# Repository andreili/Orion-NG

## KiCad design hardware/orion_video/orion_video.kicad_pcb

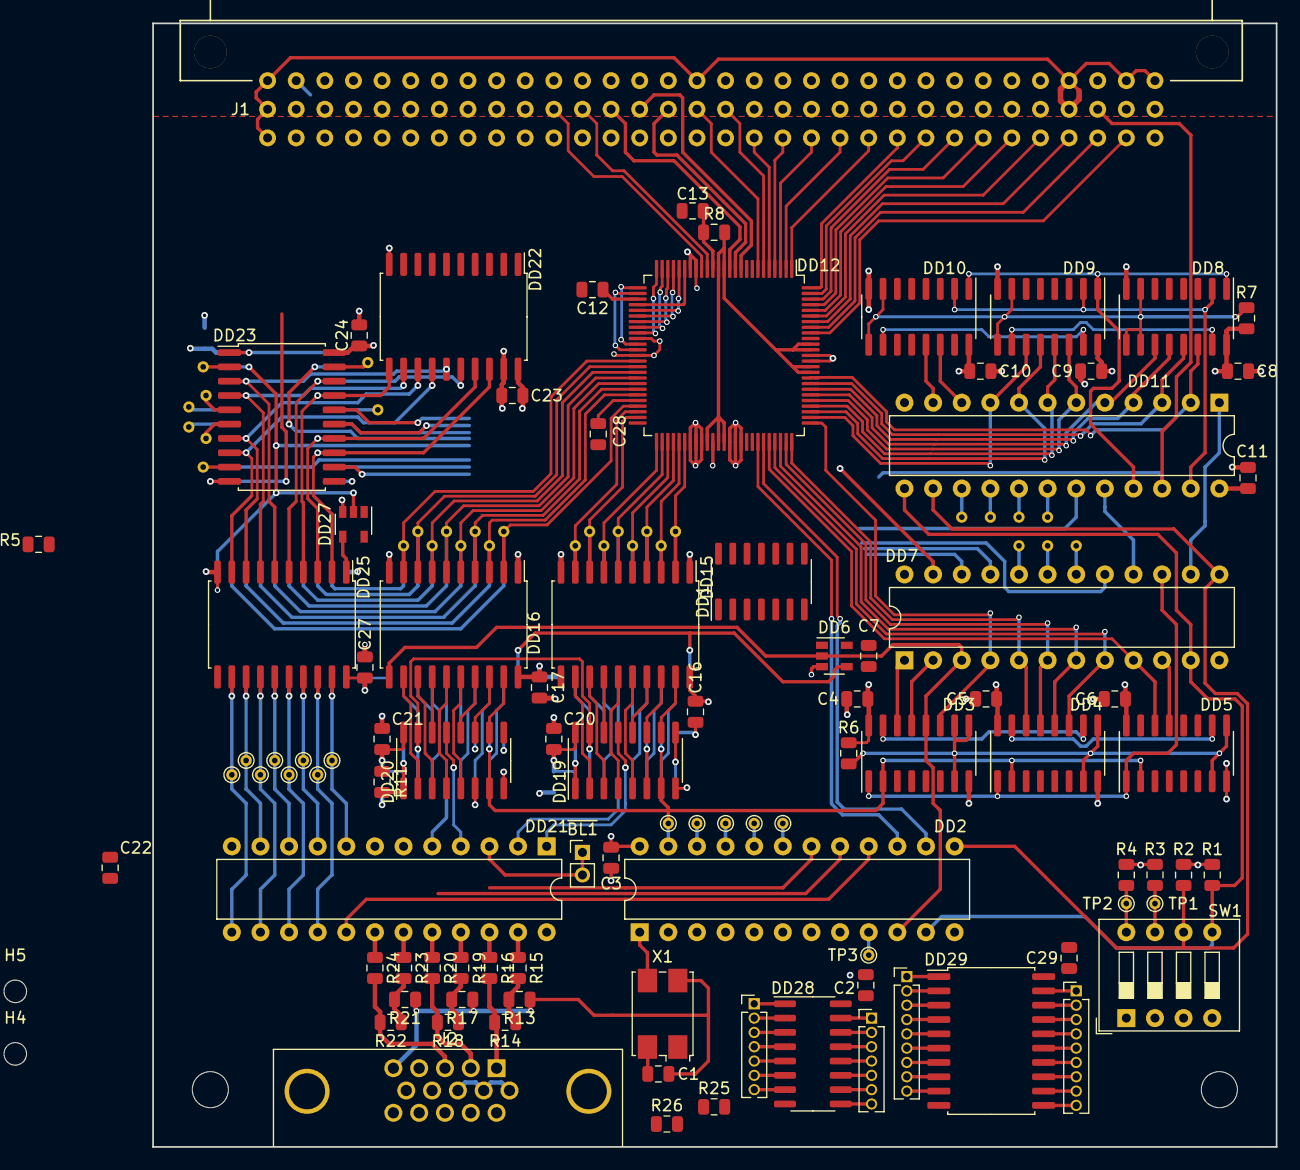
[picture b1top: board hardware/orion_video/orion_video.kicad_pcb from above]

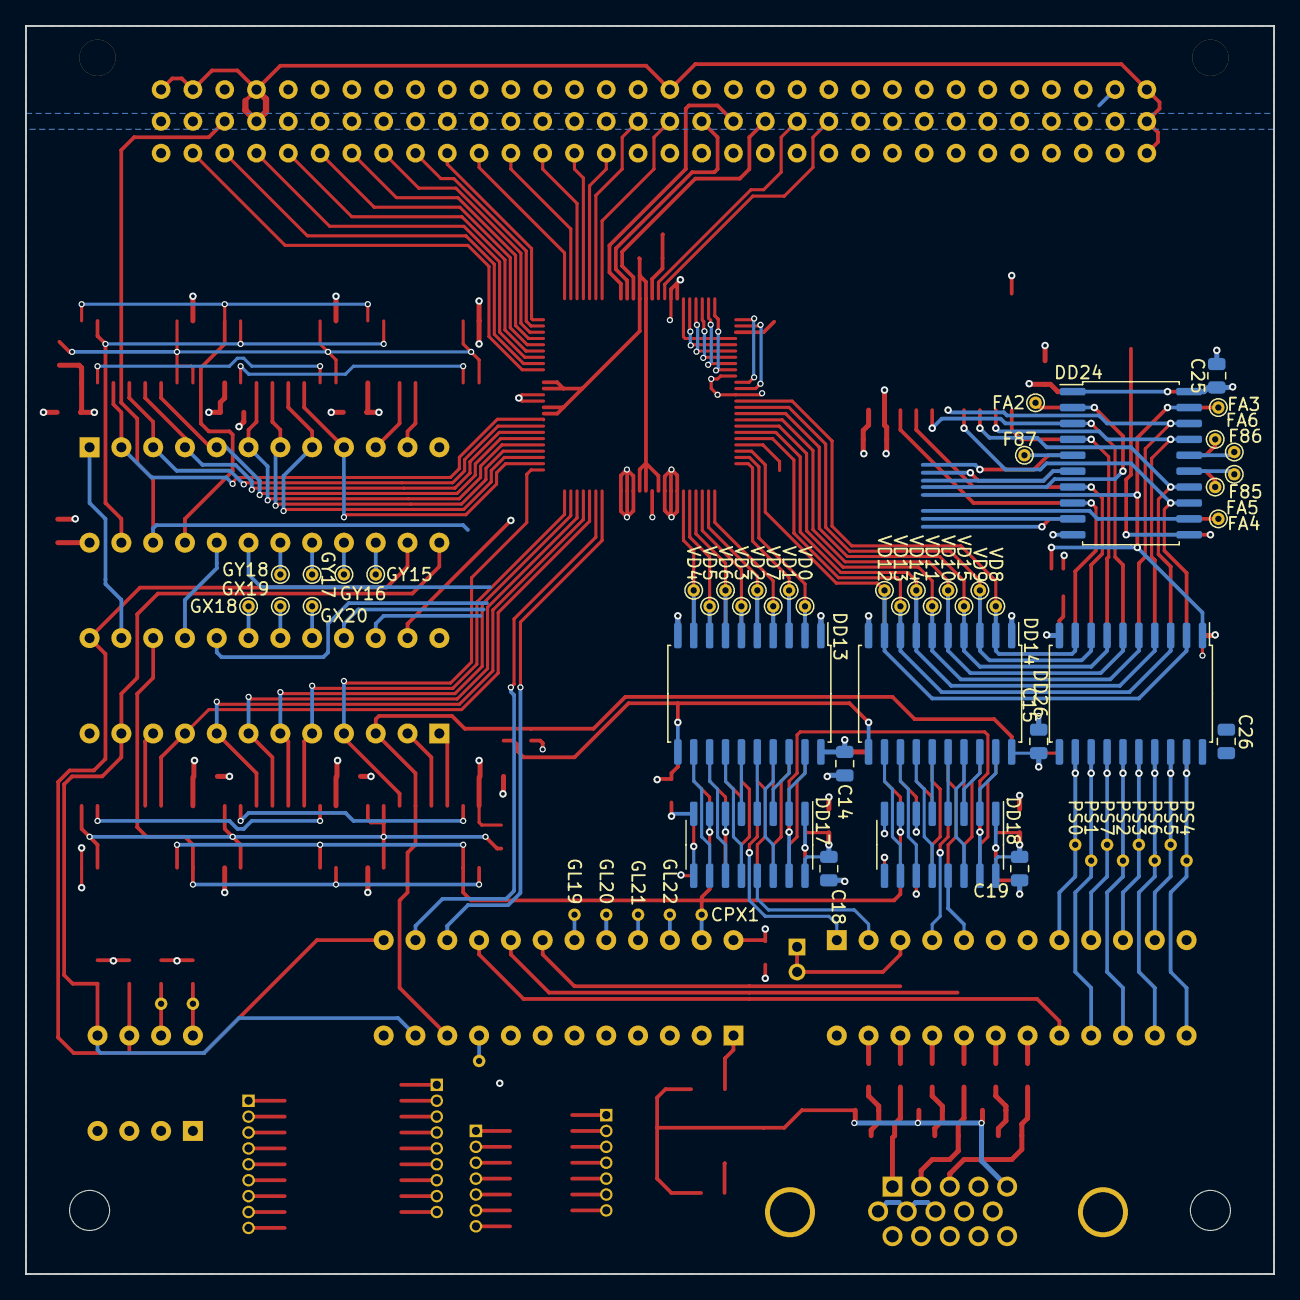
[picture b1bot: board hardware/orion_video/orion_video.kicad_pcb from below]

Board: 4 copper layers, 99.7 x 99.7 mm, 142 parts (43 on the bottom side), 232 nets.

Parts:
C1, C2, C3, C4, C5, C6, C7, C8, C9, C10, C11, C12, C13, C14, C15, C16, C17, C18, C19, C20, C21, C22, C23, C24, C25, C26, C27, C28, C29: 100n; C_0805_2012Metric
CPX1: TestPoint_Small; TestPoint_THTPad_D1.0mm_Drill0.5mm
DD1: TM2; SOIC-14_3.9x8.7mm_P1.27mm
DD2, DD7, DD11, DD21: ATF22V10; DIP-24_W7.62mm
DD3, DD4, DD5, DD8, DD9, DD10: IE18; SOIC-16_3.9x9.9mm_P1.27mm
DD6: 74AHCT1GU04; SOT-23-5
DD12: IDT7028PF; LQFP-100_14x14mm_P0.5mm
DD13, DD14, DD15, DD16: IR33; SOIC-20W_7.5x12.8mm_P1.27mm
DD17, DD18, DD19, DD20: IR10; SOIC-16_3.9x9.9mm_P1.27mm
DD22: AP6; SOIC-20W_7.5x12.8mm_P1.27mm
DD23, DD24: IR35; SOIC-20W_7.5x12.8mm_P1.27mm
DD25: 6; SOIC-20W_7.5x12.8mm_P1.27mm
DD26: IR23; SOIC-20W_7.5x12.8mm_P1.27mm
DD27: 74AHC1G04; SOT-23-5
DD28: Conn_02x08_Counter_Clockwise; SOIC-16_3.9x9.9mm_P1.27mm
DD29: Conn_02x10_Counter_Clockwise; SOIC-20W_7.5x12.8mm_P1.27mm
F85, F86, F87: FA2; TestPoint_THTPad_D1.0mm_Drill0.5mm
FA2: FA2; TestPoint_THTPad_D1.0mm_Drill0.5mm
FA3: FA3; TestPoint_THTPad_D1.0mm_Drill0.5mm
FA4: FA4; TestPoint_THTPad_D1.0mm_Drill0.5mm
FA5: FA5; TestPoint_THTPad_D1.0mm_Drill0.5mm
FA6: FA6; TestPoint_THTPad_D1.0mm_Drill0.5mm
GL19: GL14; TestPoint_THTPad_D1.0mm_Drill0.5mm
GL20: GL15; TestPoint_THTPad_D1.0mm_Drill0.5mm
GL21: GL16; TestPoint_THTPad_D1.0mm_Drill0.5mm
GL22: GL22; TestPoint_THTPad_D1.0mm_Drill0.5mm
GX18: GX18; TestPoint_THTPad_D1.0mm_Drill0.5mm
GX19: GX19; TestPoint_THTPad_D1.0mm_Drill0.5mm
GX20: GX20; TestPoint_THTPad_D1.0mm_Drill0.5mm
GY15: GY15; TestPoint_THTPad_D1.0mm_Drill0.5mm
GY16: GY16; TestPoint_THTPad_D1.0mm_Drill0.5mm
GY17: GY17; TestPoint_THTPad_D1.0mm_Drill0.5mm
GY18: GY22; TestPoint_THTPad_D1.0mm_Drill0.5mm
H1, H2: MountingHole; MountingHole_3.2mm_M3
H3, H4, H5, H6: MountingHole; MountingHole_2mm
J1: C96ABC; Socket_DIN41612-CaseC1-full-Male-96Pin-3rows
J2: VGA; DSUB-15-HD_Female_Horizontal_P2.29x1.98mm_EdgePinOffset3.03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
J3, J4: Conn_01x07_Female; PinHeader_1x07_P1.27mm_Vertical
J5, J6: Conn_01x09_Female; PinHeader_1x09_P1.27mm_Vertical
PS0, PS1, PS2, PS3, PS4, PS5, PS6, PS7: TestPoint_Small; TestPoint_THTPad_D1.0mm_Drill0.5mm
R1, R2, R3, R4, R5, R6, R7, R15, R19, R23: 1K; R_0805_2012Metric
R8, R11: 1k; R_0805_2012Metric
R13, R14, R17, R18, R21, R22: 470; R_0805_2012Metric
R16, R20, R24: 510; R_0805_2012Metric
R25, R26: 47; R_0805_2012Metric
SW1: SW_DIP_04; SW_DIP_SPSTx04_Slide_9.78x12.34mm_W7.62mm_P2.54mm
TP1: SW2; TestPoint_THTPad_D1.0mm_Drill0.5mm
TP2: SW3; TestPoint_THTPad_D1.0mm_Drill0.5mm
TP3: GL13; TestPoint_THTPad_D1.0mm_Drill0.5mm
VD0, VD1, VD2, VD3, VD4, VD5, VD6, VD7, VD8, VD9, VD10, VD11, VD12, VD13, VD14, VD15: TestPoint_Small; TestPoint_THTPad_D1.0mm_Drill0.5mm
X1: 50MHz; Crystal_SMD_7050-4Pin_7.0x5.0mm

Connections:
/CL0: DD6.4, DD13.11 (LE), DD14.11 (LE)
/CL1: DD2.10 (I10), DD3.12 (4), DD6.2, DD7.3 (I3), DD15.11 (LE), DD16.11 (LE)
/CPX: CPX1.1, DD2.23 (IO1), DD3.2 (C), DD4.2 (C), DD5.2 (C), DD17.7 (C), DD18.7 (C), DD19.7 (C), DD20.7 (C)
/FEND: DD1.3 (C), DD1.11 (C), DD11.22 (IO2), J1.30b (30B)
/HS: DD7.21 (IO3), R25.2
/SR16: DD7.23 (IO1), DD23.16 (6)
/VB0: DD1.12 (D), DD23.12 (4)
/VB1: DD1.2 (D), DD23.15 (5)
/VD0: DD12.48 (Q8), DD13.2 (0), DD15.9 (7), VD0.1
/VD1: DD12.49 (Q9), DD13.3 (1), DD15.8 (6), VD1.1
/VD2: DD12.52 (Q11), DD13.5 (3), DD15.6 (4), VD2.1
/VD3: DD12.53 (Q12), DD13.6 (4), DD15.5 (3), VD3.1
/VD4: DD12.56 (Q15), DD13.9 (7), DD15.2 (0), VD4.1
/VD5: DD12.55 (Q14), DD13.8 (6), DD15.3 (1), VD5.1
/VD6: DD12.54 (Q13), DD13.7 (5), DD15.4 (2), VD6.1
/VD7: DD12.51 (Q10), DD13.4 (2), DD15.7 (5), VD7.1
/VD8: DD12.39 (Q0), DD14.2 (0), DD16.9 (7), DD26.9 (7), VD8.1
/VD9: DD12.40 (Q1), DD14.3 (1), DD16.8 (6), DD26.8 (6), VD9.1
/VD10: DD12.42 (Q3), DD14.5 (3), DD16.6 (4), DD26.6 (4), VD10.1
/VD11: DD12.43 (Q4), DD14.6 (4), DD16.5 (3), DD26.5 (3), VD11.1
/VD12: DD12.47 (Q7), DD14.9 (7), DD16.2 (0), DD26.2 (0), VD12.1
/VD13: DD12.45 (Q6), DD14.8 (6), DD16.3 (1), DD26.3 (1), VD13.1
/VD14: DD12.44 (Q5), DD14.7 (5), DD16.4 (2), DD26.4 (2), VD14.1
/VD15: DD12.41 (Q2), DD14.4 (2), DD16.7 (5), DD26.7 (5), VD15.1
/VM0: DD2.6 (I6), DD24.9 (3)
/VM1: DD2.7 (I7), DD24.6 (2)
/VM2: DD2.5 (I5), DD18.9 (R), DD24.2 (0)
/VM3: DD2.4 (I4), DD24.19 (7), DD26.1 (OE), DD27.2
/VM4: DD2.8 (I8), DD24.12 (4)
/VS: DD11.19 (IO5), R26.2
/VS0: DD2.18 (IO6), DD21.7 (I7)
/VS1: DD2.17 (IO7), DD21.6 (I6)
/VS2: DD2.16 (IO8), DD21.17 (IO7)
/video_gen/SR0: DD2.11 (I11), DD7.11 (I11), DD11.13 (I12), R1.2, SW1.5
/video_gen/SR1: DD2.13 (I12), DD7.13 (I12), DD11.14 (IO10), R2.2, SW1.6
/video_gen/X0: DD3.14 (1), DD7.1 (I1/CLK)
/video_gen/X1: DD3.13 (2), DD7.2 (I2)
/video_gen/X3: DD3.11 (8), DD7.4 (I4), DD12.76 (A8)
/video_gen/X4: DD4.14 (1), DD7.5 (I5), DD12.75 (A9)
/video_gen/X5: DD4.13 (2), DD7.6 (I6), DD12.74 (A10)
/video_gen/X6: DD4.12 (4), DD7.7 (I7), DD12.73 (A11)
/video_gen/X7: DD4.11 (8), DD7.8 (I8), DD12.72 (A12)
/video_gen/X8: DD5.14 (1), DD7.9 (I9), DD12.71 (A13)
/video_gen/X9: DD5.13 (2), DD7.10 (I10)
/video_gen/XH0: DD3.15 (P2), DD4.10 (P1)
/video_gen/XH1: DD4.15 (P2), DD5.10 (P1)
/video_gen/XLE: DD7.14 (IO10), DD11.1 (I1/CLK)
/video_gen/Y0: DD8.14 (1), DD11.2 (I2), DD12.84 (A0)
/video_gen/Y1: DD8.13 (2), DD11.3 (I3), DD12.83 (A1)
/video_gen/Y2: DD8.12 (4), DD11.4 (I4), DD12.82 (A2)
/video_gen/Y3: DD8.11 (8), DD11.5 (I5), DD12.81 (A3)
/video_gen/Y4: DD9.14 (1), DD11.6 (I6), DD12.80 (A4)
/video_gen/Y5: DD9.13 (2), DD11.7 (I7), DD12.79 (A5)
/video_gen/Y6: DD9.12 (4), DD11.8 (I8), DD12.78 (A6)
/video_gen/Y7: DD9.11 (8), DD11.9 (I9), DD12.77 (A7)
/video_gen/Y8: DD10.14 (1), DD11.10 (I10)
/video_gen/Y9: DD10.13 (2), DD11.11 (I11)
/video_gen/YH0: DD8.15 (P2), DD9.10 (P1)
/video_gen/YH1: DD9.15 (P2), DD10.10 (P1)
/video_gen/~BV: DD7.16 (IO8), DD11.20 (IO4)
/video_gen/~XRES: DD3.1 (RC), DD4.1 (RC), DD5.1 (RC), DD7.15 (IO9)
/video_gen/~YRES: DD8.1 (RC), DD9.1 (RC), DD10.1 (RC), DD11.21 (IO3)
/video_regs/A0: DD12.92 (A0), J1.31a (31A)
/video_regs/A1: DD12.93 (A1), J1.30a (30A)
/video_regs/A2: DD12.94 (A2), J1.29a (29A)
/video_regs/A3: DD12.95 (A3), J1.28a (28A)
/video_regs/A4: DD12.96 (A4), J1.27a (27A)
/video_regs/A5: DD12.97 (A5), J1.26a (26A)
/video_regs/A6: DD12.98 (A6), J1.25a (25A)
/video_regs/A7: DD12.99 (A7), J1.24a (24A)
/video_regs/A8: DD12.100 (A8), J1.23a (23A)
/video_regs/A9: DD12.1 (A9), J1.22a (22A)
/video_regs/A10: DD12.2 (A10), J1.21a (21A)
/video_regs/A11: DD12.3 (A11), J1.20a (20A)
/video_regs/A12: DD12.4 (A12), J1.19a (19A)
/video_regs/A13: DD12.5 (A13), J1.18a (18A)
/video_regs/BD0: DD12.27 (Q8), DD12.37 (Q0), DD22.18 (B0), DD23.13 (4), DD24.8 (3), DD25.2 (0)
/video_regs/BD1: DD12.26 (Q9), DD12.36 (Q1), DD22.17 (B1), DD23.14 (5), DD24.7 (2), DD25.3 (1)
/video_regs/BD2: DD12.24 (Q11), DD12.33 (Q3), DD22.16 (B2), DD23.18 (7), DD24.3 (0), DD25.5 (3)
/video_regs/BD3: DD12.23 (Q12), DD12.32 (Q4), DD22.15 (B3), DD23.3 (0), DD24.18 (7), DD25.6 (4)
/video_regs/BD4: DD12.20 (Q15), DD12.29 (Q7), DD22.14 (B4), DD23.8 (3), DD24.13 (4), DD25.9 (7)
/video_regs/BD5: DD12.21 (Q14), DD12.30 (Q6), DD22.13 (B5), DD23.7 (2), DD24.14 (5), DD25.8 (6)
/video_regs/BD6: DD12.22 (Q13), DD12.31 (Q5), DD22.12 (B6), DD23.4 (1), DD24.17 (6), DD25.7 (5)
/video_regs/BD7: DD12.25 (Q10), DD12.34 (Q2), DD22.11 (B7), DD23.17 (6), DD24.4 (1), DD25.4 (2)
/video_regs/D0: DD22.2 (A0), J1.9a (9A)
/video_regs/D1: DD22.3 (A1), J1.8a (8A)
/video_regs/D2: DD22.4 (A2), J1.7a (7A)
/video_regs/D3: DD22.5 (A3), J1.6a (6A)
/video_regs/D4: DD22.6 (A4), J1.5a (5A)
/video_regs/D5: DD22.7 (A5), J1.4a (4A)
/video_regs/D6: DD22.8 (A6), J1.3a (3A)
/video_regs/D7: DD22.9 (A7), J1.2a (2A)
/video_regs/MA14: DD12.6 (A14), J1.17b (17B)
/video_regs/MA15: DD12.7 (A15), J1.16b (16B)
/video_regs/MA16: DD12.11 (UB), J1.15b (15B)
/video_regs/P0: DD17.13 (QH), DD21.2 (I2)
/video_regs/P1: DD18.13 (QH), DD21.5 (I5)
/video_regs/P2: DD19.13 (QH), DD21.1 (I1/CLK)
/video_regs/P3: DD20.13 (QH), DD21.4 (I4)
/video_regs/PF8: DD24.11 (C), J1.7b (7B)
/video_regs/PFA: DD23.11 (C), J1.8b (8B)
/video_regs/PFC: DD25.11 (C), J1.6b (6B)
/video_regs/PS0: DD21.8 (I8), DD25.19 (0), DD26.12 (7), PS0.1
/video_regs/PS1: DD21.16 (IO8), DD25.18 (1), DD26.13 (6), PS1.1
/video_regs/PS2: DD21.15 (IO9), DD25.16 (3), DD26.15 (4), PS2.1
/video_regs/PS3: DD21.10 (I10), DD25.15 (4), DD26.16 (3), PS3.1
/video_regs/PS4: DD21.13 (I12), DD25.12 (7), DD26.19 (0), PS4.1
/video_regs/PS5: DD21.11 (I11), DD25.13 (6), DD26.18 (1), PS5.1
/video_regs/PS6: DD21.14 (IO10), DD25.14 (5), DD26.17 (2), PS6.1
/video_regs/PS7: DD21.9 (I9), DD25.17 (2), DD26.14 (5), PS7.1
/video_regs/~MRD: DD12.17 (~OE), J1.11b (11B)
/video_regs/~MWR: DD12.16 (R/~W), J1.12b (12B)
/video_regs/~RD: DD22.1 (A/B), J1.14c (14C)
/video_regs/~RES: DD23.1 (R), DD24.1 (R), J1.2c (2C)
/video_regs/~UB: DD12.10 (LB), J1.14b (14B)
/video_regs/~VCE: DD12.12 (~CE0), J1.13b (13B)
/~BE: DD7.22 (IO2), DD17.15 (L), DD18.15 (L), DD19.15 (L), DD20.15 (L), DD26.11 (C)
/~BL: DD7.17 (IO7), DD21.3 (I3)
GND: C1.2, C2.2, C3.2, C4.2, C5.2, C6.2, C7.2, C8.2, C9.2, C10.2, C11.2, C12.2, C13.2, C14.2, C15.2, C16.2, C17.2, C18.2, C19.2, C20.2, C21.2, C22.2, C23.2, C24.2, C25.2, C26.2, C27.2, C28.2, C29.2, DD1.7 (GND), DD2.12 (GND), DD3.8 (GND), DD4.8 (GND), DD5.8 (GND), DD6.3 (GND), DD7.12 (GND), DD8.8 (GND), DD9.8 (GND), DD10.8 (GND), DD11.12 (GND), DD12.18 (GND), DD12.19 (GND), DD12.35 (GND), DD12.38 (GND), DD12.57 (GND), DD12.58 (GND), DD12.59 (~OE), DD12.61 (GND), DD12.64 (~CE0), DD12.65 (UB), DD12.66 (LB), DD12.87 (M/~S), DD12.88 (GND), DD13.1 (OE), DD13.10 (GND), DD14.1 (OE), DD14.10 (GND), DD15.1 (OE), DD15.10 (GND), DD16.1 (OE), DD16.10 (GND), DD17.6 (CI), DD17.8 (GND), DD18.6 (CI), DD18.8 (GND), DD19.6 (CI), DD19.8 (GND), DD20.6 (CI), DD20.8 (GND), DD21.12 (GND), DD22.10 (GND), DD22.19 (OE), DD23.10 (GND), DD24.10 (GND), DD25.10 (GND), DD26.10 (GND), DD27.3 (GND), DD28.8, DD29.10, J1.1a (1A), J1.1b (1B), J1.1c (1C), J1.16c (16C), J1.29b (29B), J1.29c (29C), J1.31c (31C), J1.32c (32C), J2.5, J2.6, J2.7, J2.8, J2.10, R13.1, R17.1, R21.1, SW1.1, SW1.2, SW1.3, SW1.4, X1.2 (GND)
MVP: DD12.13 (CE1), DD12.14 (~SEM), DD12.60 (R/~W), DD12.62 (~SEM), DD12.63 (CE1), DD12.85 (~INTL), DD12.86 (~BUSY), DD12.89 (~BUSY), DD12.90 (~INTL), R8.2
unnamed: DD1.1 (R), DD1.4 (S), DD1.10 (S), DD1.13 (R), R5.2
unnamed: DD1.6 (Q), DD2.3 (I3)
unnamed: DD1.8 (Q), DD2.2 (I2)
unnamed: DD2.1 (I1/CLK), X1.3 (OUT)
unnamed: DD2.9 (I9), TP3.1
unnamed: DD2.19 (IO5), GL19.1
unnamed: DD2.20 (IO4), GL20.1
unnamed: DD2.21 (IO3), GL21.1
unnamed: DD2.22 (IO2), GL22.1
unnamed: DD3.7 (V1), DD3.9 (W), DD3.10 (P1), DD4.7 (V1), DD4.9 (W), DD5.7 (V1), DD5.9 (W), R6.2
unnamed: DD7.18 (IO6), GX18.1
unnamed: DD7.19 (IO5), GX19.1
unnamed: DD7.20 (IO4), GX20.1
unnamed: DD8.2 (C), DD9.2 (C), DD10.2 (C), DD11.23 (IO1)
unnamed: DD8.7 (V1), DD8.9 (W), DD8.10 (P1), DD9.7 (V1), DD9.9 (W), DD10.7 (V1), DD10.9 (W), R7.2
unnamed: DD11.15 (IO9), GY15.1
unnamed: DD11.16 (IO8), GY16.1
unnamed: DD11.17 (IO7), GY17.1
unnamed: DD11.18 (IO6), GY18.1
unnamed: DD2.15 (IO9), DD12.69 (A15)
unnamed: DD2.14 (IO10), DD12.70 (A14)
unnamed: DD17.1 (SI), DD17.9 (R), DD18.1 (SI), DD19.1 (SI), DD19.9 (R), DD20.1 (SI), DD20.9 (R), R11.2
unnamed: DD21.18 (IO6), R24.1
unnamed: DD21.19 (IO5), R23.1
unnamed: DD21.20 (IO4), R20.1
unnamed: DD21.21 (IO3), R19.1
unnamed: DD21.22 (IO2), R16.1
unnamed: DD21.23 (IO1), R15.1
unnamed: DD23.2 (0), FA3.1
unnamed: DD23.5 (1), FA6.1
unnamed: DD23.6 (2), FA5.1
unnamed: DD23.9 (3), FA4.1
unnamed: DD23.19 (7), FA2.1
unnamed: DD24.5 (1), F87.1
unnamed: DD24.15 (5), F85.1
unnamed: DD24.16 (6), F86.1
unnamed: DD25.1 (OE), DD27.4
unnamed: DD28.1, J3.1
unnamed: DD28.2, J3.2
unnamed: DD28.3, J3.3
unnamed: DD28.4, J3.4
unnamed: DD28.5, J3.5
unnamed: DD28.6, J3.6
unnamed: DD28.7, J3.7
unnamed: DD28.9, J4.7
unnamed: DD28.10, J4.6
unnamed: DD28.11, J4.5
unnamed: DD28.12, J4.4
unnamed: DD28.13, J4.3
unnamed: DD28.14, J4.2
unnamed: DD28.15, J4.1
unnamed: DD29.1, J5.1
unnamed: DD29.2, J5.2
unnamed: DD29.3, J5.3
unnamed: DD29.4, J5.4
unnamed: DD29.5, J5.5
unnamed: DD29.6, J5.6
unnamed: DD29.7, J5.7
unnamed: DD29.8, J5.8
unnamed: DD29.9, J5.9
unnamed: DD29.11, J6.9
unnamed: DD29.12, J6.8
unnamed: DD29.13, J6.7
unnamed: DD29.14, J6.6
unnamed: DD29.15, J6.5
unnamed: DD29.16, J6.4
unnamed: DD29.17, J6.3
unnamed: DD29.18, J6.2
unnamed: DD29.19, J6.1
unnamed: J2.1, R14.2, R16.2
unnamed: J2.2, R18.2, R20.2
unnamed: J2.3, R22.2, R24.2
unnamed: J2.13, R25.1
unnamed: J2.14, R26.1
unnamed: R3.2, SW1.7, TP1.1
unnamed: R4.2, SW1.8, TP2.1
unnamed: R13.2, R14.1, R15.2
unnamed: R17.2, R18.1, R19.2
unnamed: R21.2, R22.1, R23.2
VCC: C1.1, C2.1, C3.1, C4.1, C5.1, C6.1, C7.1, C8.1, C9.1, C10.1, C11.1, C12.1, C13.1, C14.1, C15.1, C16.1, C17.1, C18.1, C19.1, C20.1, C21.1, C22.1, C23.1, C24.1, C25.1, C26.1, C27.1, C28.1, C29.1, DD1.14 (VCC), DD2.24 (VCC), DD3.16 (VCC), DD4.16 (VCC), DD5.16 (VCC), DD6.5 (VCC), DD7.24 (VCC), DD8.16 (VCC), DD9.16 (VCC), DD10.16 (VCC), DD11.24 (VCC), DD12.15 (VCC), DD12.28 (VCC), DD12.46 (VCC), DD13.20 (VCC), DD14.20 (VCC), DD15.20 (VCC), DD16.20 (VCC), DD17.16 (VCC), DD18.16 (VCC), DD19.16 (VCC), DD20.16 (VCC), DD21.24 (VCC), DD22.20 (VCC), DD23.20 (VCC), DD24.20 (VCC), DD25.20 (VCC), DD26.20 (VCC), DD27.5 (VCC), DD28.16, DD29.20, J1.3b (3B), J1.3c (3C), J1.18b (18B), J1.18c (18C), J1.20b (20B), J1.20c (20C), R1.1, R2.1, R3.1, R4.1, R5.1, R6.1, R7.1, R8.1, R11.1, X1.4 (V+)
VL0: DD13.19 (0), DD17.2 (0)
VL1: DD13.18 (1), DD17.3 (1)
VL2: DD13.16 (3), DD17.4 (2)
VL3: DD13.15 (4), DD17.5 (3)
VL4: DD13.12 (7), DD17.10 (4)
VL5: DD13.13 (6), DD17.11 (5)
VL6: DD13.14 (5), DD17.12 (6)
VL7: DD13.17 (2), DD17.14 (7)
VL8: DD14.19 (0), DD18.2 (0)
VL9: DD14.18 (1), DD18.3 (1)
VL10: DD14.16 (3), DD18.4 (2)
VL11: DD14.15 (4), DD18.5 (3)
VL12: DD14.12 (7), DD18.10 (4)
VL13: DD14.13 (6), DD18.11 (5)
VL14: DD14.14 (5), DD18.12 (6)
VL15: DD14.17 (2), DD18.14 (7)
VL16: DD15.12 (7), DD19.2 (0)
VL17: DD15.13 (6), DD19.3 (1)
VL18: DD15.15 (4), DD19.4 (2)
VL19: DD15.16 (3), DD19.5 (3)
VL20: DD15.19 (0), DD19.10 (4)
VL21: DD15.18 (1), DD19.11 (5)
VL22: DD15.17 (2), DD19.12 (6)
VL23: DD15.14 (5), DD19.14 (7)
VL24: DD16.12 (7), DD20.2 (0)
VL25: DD16.13 (6), DD20.3 (1)
VL26: DD16.15 (4), DD20.4 (2)
VL27: DD16.16 (3), DD20.5 (3)
VL28: DD16.19 (0), DD20.10 (4)
VL29: DD16.18 (1), DD20.11 (5)
VL30: DD16.17 (2), DD20.12 (6)
VL31: DD16.14 (5), DD20.14 (7)

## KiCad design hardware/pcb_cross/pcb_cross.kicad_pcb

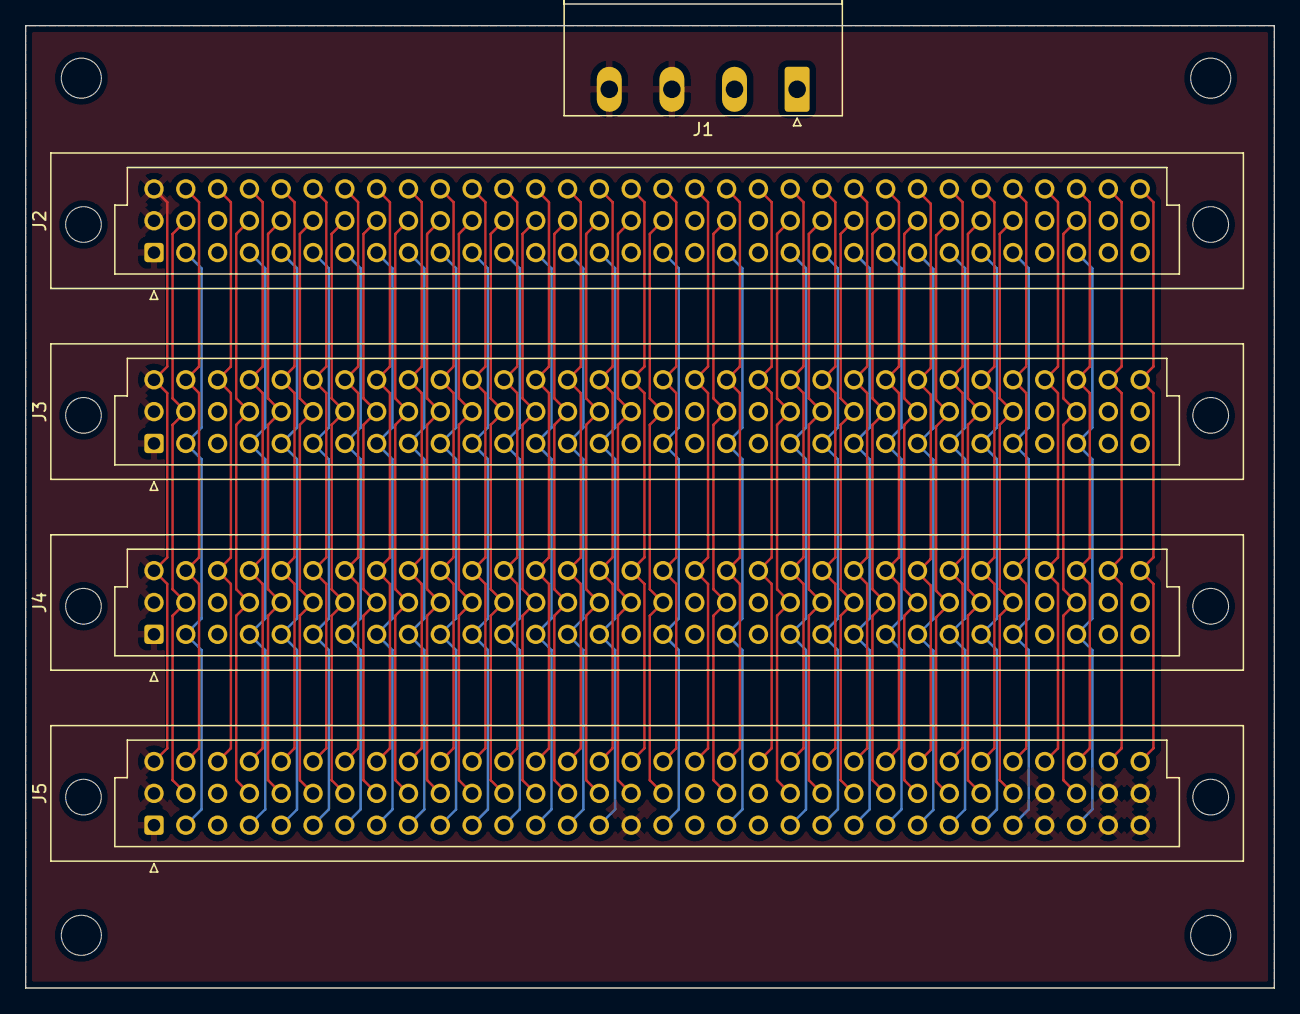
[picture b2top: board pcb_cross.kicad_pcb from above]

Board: 4 copper layers, 99.7 x 76.8 mm, 5 parts (0 on the bottom side), 82 nets.

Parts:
J1: Screw_Terminal_01x04; PhoenixContact_MSTBA_2,5_4-G_1x04_P5.00mm_Horizontal
J2, J3, J4, J5: C96ABC; DIN41612_C_3x32_Female_Vertical_THT

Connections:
/A0: J2.c31 (C31), J3.c31 (C31), J4.c31 (C31), J5.c31 (C31)
/A1: J2.c30 (C30), J3.c30 (C30), J4.c30 (C30), J5.c30 (C30)
/A2: J2.c29 (C29), J3.c29 (C29), J4.c29 (C29), J5.c29 (C29)
/A3: J2.c28 (C28), J3.c28 (C28), J4.c28 (C28), J5.c28 (C28)
/A4: J2.c27 (C27), J3.c27 (C27), J4.c27 (C27), J5.c27 (C27)
/A5: J2.c26 (C26), J3.c26 (C26), J4.c26 (C26), J5.c26 (C26)
/A6: J2.c25 (C25), J3.c25 (C25), J4.c25 (C25), J5.c25 (C25)
/A7: J2.c24 (C24), J3.c24 (C24), J4.c24 (C24), J5.c24 (C24)
/A8: J2.c23 (C23), J3.c23 (C23), J4.c23 (C23), J5.c23 (C23)
/A9: J2.c22 (C22), J3.c22 (C22), J4.c22 (C22), J5.c22 (C22)
/A10: J2.c21 (C21), J3.c21 (C21), J4.c21 (C21), J5.c21 (C21)
/A11: J2.c20 (C20), J3.c20 (C20), J4.c20 (C20), J5.c20 (C20)
/A12: J2.c19 (C19), J3.c19 (C19), J4.c19 (C19), J5.c19 (C19)
/A13: J2.c18 (C18), J3.c18 (C18), J4.c18 (C18), J5.c18 (C18)
/A14: J2.c17 (C17), J3.c17 (C17), J4.c17 (C17), J5.c17 (C17)
/A15: J2.c16 (C16), J3.c16 (C16), J4.c16 (C16), J5.c16 (C16)
/D0': J2.c9 (C9), J3.c9 (C9), J4.c9 (C9), J5.c9 (C9)
/D1': J2.c8 (C8), J3.c8 (C8), J4.c8 (C8), J5.c8 (C8)
/D2': J2.c7 (C7), J3.c7 (C7), J4.c7 (C7), J5.c7 (C7)
/D3': J2.c6 (C6), J3.c6 (C6), J4.c6 (C6), J5.c6 (C6)
/D4': J2.c5 (C5), J3.c5 (C5), J4.c5 (C5), J5.c5 (C5)
/D5': J2.c4 (C4), J3.c4 (C4), J4.c4 (C4), J5.c4 (C4)
/D6': J2.c3 (C3), J3.c3 (C3), J4.c3 (C3), J5.c3 (C3)
/D7': J2.c2 (C2), J3.c2 (C2), J4.c2 (C2), J5.c2 (C2)
/FEND: J2.b19 (B19), J3.b19 (B19), J4.b19 (B19), J5.b19 (B19)
/HLDA: J2.c32 (C32), J3.c32 (C32), J4.c32 (C32), J5.c32 (C32)
/HOLD: J2.a15 (A15), J3.a15 (A15), J4.a15 (A15), J5.a15 (A15)
/IORQ: J2.a11 (A11), J3.a11 (A11), J4.a11 (A11), J5.a11 (A11)
/M1: J2.a6 (A6), J3.a6 (A6), J4.a6 (A6), J5.a6 (A6)
/MA14: J2.b17 (B17), J3.b17 (B17), J4.b17 (B17), J5.b17 (B17)
/MA15: J2.b16 (B16), J3.b16 (B16), J4.b16 (B16), J5.b16 (B16)
/MA16: J2.b15 (B15), J3.b15 (B15), J4.b15 (B15), J5.b15 (B15)
/MA17: J2.b14 (B14), J3.b14 (B14), J4.b14 (B14), J5.b14 (B14)
/MA18: J2.b13 (B13), J3.b13 (B13), J4.b13 (B13), J5.b13 (B13)
/MA19: J2.b12 (B12), J3.b12 (B12), J4.b12 (B12), J5.b12 (B12)
/MA20: J2.b11 (B11), J3.b11 (B11), J4.b11 (B11), J5.b11 (B11)
/MREQ: J2.a12 (A12), J3.a12 (A12), J4.a12 (A12), J5.a12 (A12)
/RD: J2.a14 (A14), J3.a14 (A14), J4.a14 (A14), J5.a14 (A14)
/RES: J2.a2 (A2), J3.a2 (A2), J4.a2 (A2), J5.a2 (A2)
/RFSH: J2.a19 (A19), J3.a19 (A19), J4.a19 (A19), J5.a19 (A19)
/WR: J2.a13 (A13), J3.a13 (A13), J4.a13 (A13), J5.a13 (A13)
/X0: J2.a30 (A30), J3.a30 (A30), J4.a30 (A30), J5.a30 (A30)
/X1: J2.a17 (A17), J3.a17 (A17), J4.a17 (A17), J5.a17 (A17)
/a5: J2.a5 (A5), J3.a5 (A5), J4.a5 (A5), J5.a5 (A5)
/a7: J2.a7 (A7), J3.a7 (A7), J4.a7 (A7), J5.a7 (A7)
/a9: J2.a9 (A9), J3.a9 (A9), J4.a9 (A9), J5.a9 (A9)
/b2: J2.b2 (B2), J3.b2 (B2), J4.b2 (B2), J5.b2 (B2)
/b4: J2.b4 (B4), J3.b4 (B4), J4.b4 (B4), J5.b4 (B4)
/b5: J2.b5 (B5), J3.b5 (B5), J4.b5 (B5), J5.b5 (B5)
/b6: J2.b6 (B6), J3.b6 (B6), J4.b6 (B6), J5.b6 (B6)
/b7: J2.b7 (B7), J3.b7 (B7), J4.b7 (B7), J5.b7 (B7)
/b8: J2.b8 (B8), J3.b8 (B8), J4.b8 (B8), J5.b8 (B8)
/b9: J2.b9 (B9), J3.b9 (B9), J4.b9 (B9), J5.b9 (B9)
/b10: J2.b10 (B10), J3.b10 (B10), J4.b10 (B10), J5.b10 (B10)
/b21: J2.b21 (B21), J3.b21 (B21), J4.b21 (B21), J5.b21 (B21)
/b22: J2.b22 (B22), J3.b22 (B22), J4.b22 (B22), J5.b22 (B22)
/b23: J2.b23 (B23), J3.b23 (B23), J4.b23 (B23), J5.b23 (B23)
/b24: J2.b24 (B24), J3.b24 (B24), J4.b24 (B24), J5.b24 (B24)
/b25: J2.b25 (B25), J3.b25 (B25), J4.b25 (B25), J5.b25 (B25)
/b26: J2.b26 (B26), J3.b26 (B26), J4.b26 (B26), J5.b26 (B26)
/b27: J2.b27 (B27), J3.b27 (B27), J4.b27 (B27), J5.b27 (B27)
/b28: J2.b28 (B28), J3.b28 (B28), J4.b28 (B28), J5.b28 (B28)
/b30: J2.b30 (B30), J3.b30 (B30), J4.b30 (B30), J5.b30 (B30)
/c11: J2.c11 (C11), J3.c11 (C11), J4.c11 (C11), J5.c11 (C11)
/c12: J2.c12 (C12), J3.c12 (C12), J4.c12 (C12), J5.c12 (C12)
/c13: J2.c13 (C13), J3.c13 (C13), J4.c13 (C13), J5.c13 (C13)
/c14: J2.c14 (C14), J3.c14 (C14), J4.c14 (C14), J5.c14 (C14)
/c15: J2.c15 (C15), J3.c15 (C15), J4.c15 (C15), J5.c15 (C15)
/~BLIO: J2.a10 (A10), J3.a10 (A10), J4.a10 (A10), J5.a10 (A10)
/~BLRAM: J2.a8 (A8), J3.a8 (A8), J4.a8 (A8), J5.a8 (A8)
/~INTA: J2.a4 (A4), J3.a4 (A4), J4.a4 (A4), J5.a4 (A4)
/~IRQ1: J2.a21 (A21), J3.a21 (A21), J4.a21 (A21), J5.a21 (A21)
/~IRQ2: J2.a22 (A22), J3.a22 (A22), J4.a22 (A22), J5.a22 (A22)
/~IRQ3: J2.a23 (A23), J3.a23 (A23), J4.a23 (A23), J5.a23 (A23)
/~IRQ4: J2.a24 (A24), J3.a24 (A24), J4.a24 (A24), J5.a24 (A24)
/~IRQ5: J2.a25 (A25), J3.a25 (A25), J4.a25 (A25), J5.a25 (A25)
/~IRQ6: J2.a26 (A26), J3.a26 (A26), J4.a26 (A26), J5.a26 (A26)
/~IRQ7: J2.a27 (A27), J3.a27 (A27), J4.a27 (A27), J5.a27 (A27)
/~IRQS: J2.a28 (A28), J3.a28 (A28), J4.a28 (A28), J5.a28 (A28)
/~WAIT: J2.c10 (C10), J3.c10 (C10), J4.c10 (C10), J5.c10 (C10)
GND: J1.3, J1.4, J2.a1 (A1), J2.a16 (A16), J2.a29 (A29), J2.a31 (A31), J2.a32 (A32), J2.b1 (B1), J2.b29 (B29), J2.b31 (B31), J2.b32 (B32), J2.c1 (C1), J3.a1 (A1), J3.a16 (A16), J3.a29 (A29), J3.a31 (A31), J3.a32 (A32), J3.b1 (B1), J3.b29 (B29), J3.b31 (B31), J3.b32 (B32), J3.c1 (C1), J4.a1 (A1), J4.a16 (A16), J4.a29 (A29), J4.a31 (A31), J4.a32 (A32), J4.b1 (B1), J4.b29 (B29), J4.b31 (B31), J4.b32 (B32), J4.c1 (C1), J5.a1 (A1), J5.a16 (A16), J5.a29 (A29), J5.a31 (A31), J5.a32 (A32), J5.b1 (B1), J5.b29 (B29), J5.b31 (B31), J5.b32 (B32), J5.c1 (C1)
VCC: J1.1, J1.2, J2.a3 (A3), J2.a18 (A18), J2.a20 (A20), J2.b3 (B3), J2.b18 (B18), J2.b20 (B20), J3.a3 (A3), J3.a18 (A18), J3.a20 (A20), J3.b3 (B3), J3.b18 (B18), J3.b20 (B20), J4.a3 (A3), J4.a18 (A18), J4.a20 (A20), J4.b3 (B3), J4.b18 (B18), J4.b20 (B20), J5.a3 (A3), J5.a18 (A18), J5.a20 (A20), J5.b3 (B3), J5.b18 (B18), J5.b20 (B20)

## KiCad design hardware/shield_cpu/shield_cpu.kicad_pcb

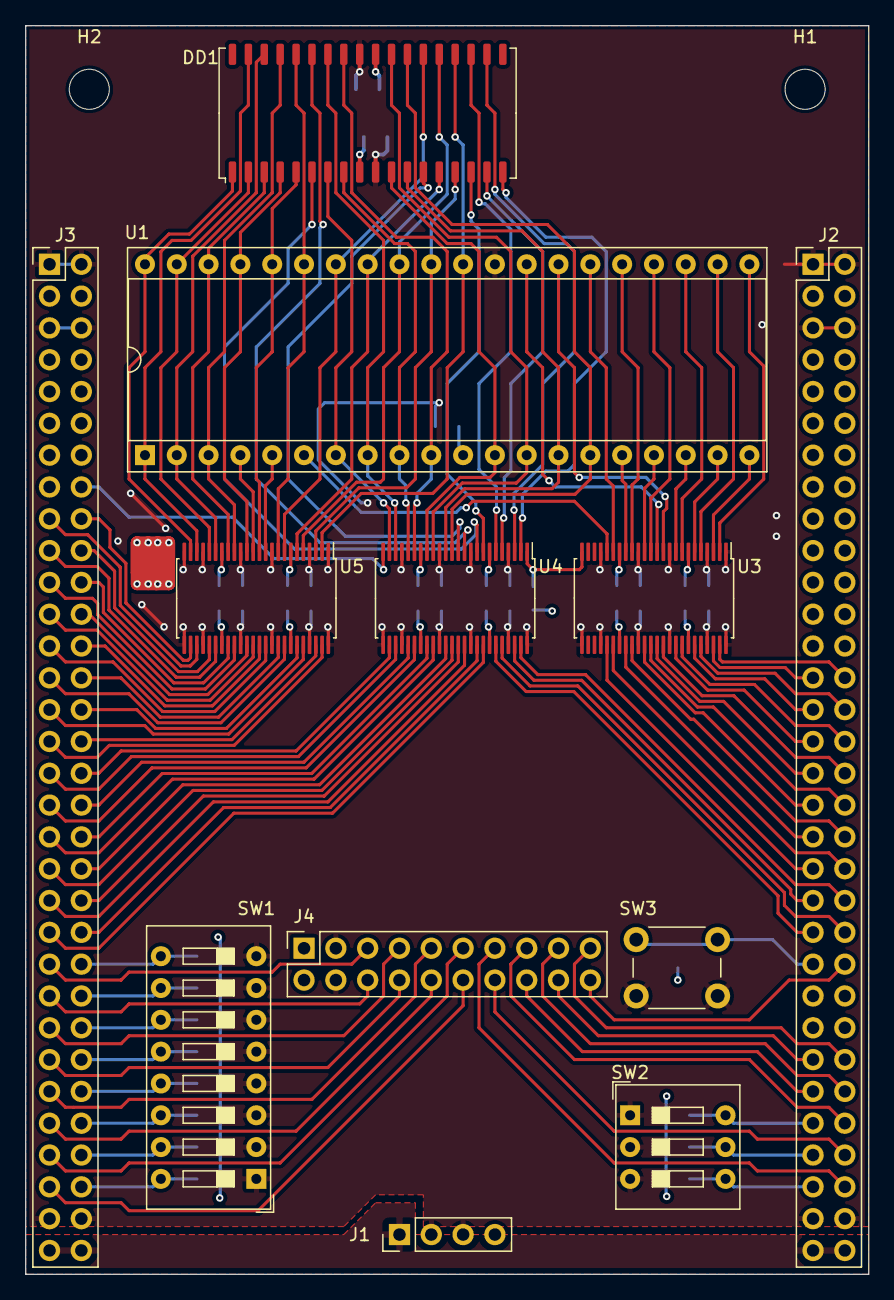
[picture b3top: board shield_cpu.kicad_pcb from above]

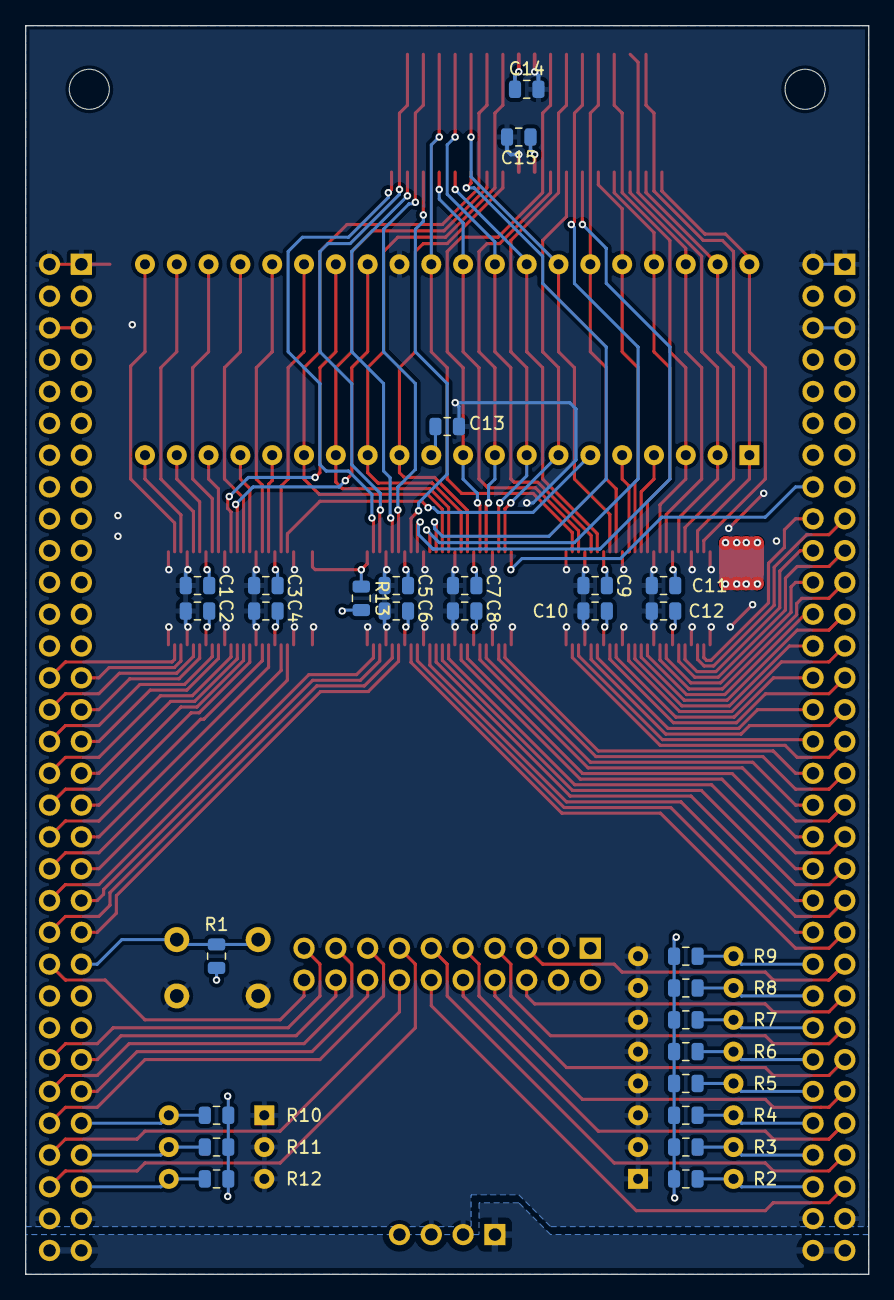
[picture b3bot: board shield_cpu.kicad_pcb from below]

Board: 4 copper layers, 67.3 x 99.7 mm, 42 parts (28 on the bottom side), 125 nets.

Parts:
C1, C2, C3, C4, C5, C6, C7, C8, C9, C10, C11, C12, C13, C14, C15: 10n; C_0805_2012Metric
DD1: CY7C1049D; SOJ-36_10.16x23.49mm_P1.27mm
H1, H2: MountingHole; MountingHole_3.2mm_M3
J1: Conn_01x04_Male; PinHeader_1x04_P2.54mm_Vertical
J2: U7; PinHeader_2x32_P2.54mm_Vertical
J3: U8; PinHeader_2x32_P2.54mm_Vertical
J4: EXT; PinSocket_2x10_P2.54mm_Vertical
R1, R2, R3, R4, R5, R6, R7, R8, R9, R10, R11, R12, R13: 1k; R_0805_2012Metric
SW1: SW_DIP_x08; SW_DIP_SPSTx08_Slide_9.78x22.5mm_W7.62mm_P2.54mm
SW2: SW_DIP_x03; SW_DIP_SPSTx03_Slide_9.78x9.8mm_W7.62mm_P2.54mm
SW3: SW_Push; SW_PUSH_6mm
U1: Z80CPU; DIP-40_W15.24mm_Socket
U3, U4, U5: 74ALVC164245; TSSOP-48_6.1x12.5mm_P0.5mm

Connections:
+3V3: C2.1, C4.1, C6.1, C8.1, C10.1, C12.1, J1.4, J2.3, J2.4, J3.3, J3.4, J4.2, R1.2, R2.2, R3.2, R4.2, R5.2, R6.2, R7.2, R8.2, R9.2, R10.2, R11.2, R12.2, R13.2, U3.31 (VCCA), U3.42 (VCCA), U4.31 (VCCA), U4.42 (VCCA), U5.31 (VCCA), U5.42 (VCCA)
+5V: C1.1, C3.1, C5.1, C7.1, C9.1, C11.1, C13.1, C14.1, C15.1, DD1.9 (VCC), DD1.27 (VCC), J1.1, J2.63, J2.64, J3.63, J3.64, J4.1, U1.11 (VCC), U3.7 (VCCB), U3.18 (VCCB), U4.7 (VCCB), U4.18 (VCCB), U5.7 (VCCB), U5.18 (VCCB)
/A0: DD1.22 (A12), U1.30 (A0), U5.2 (B0)
/A1: DD1.15 (A6), U1.31 (A1), U5.3 (B1)
/A2: DD1.23 (A13), U1.32 (A2), U5.5 (B2)
/A3: DD1.14 (A5), U1.33 (A3), U5.6 (B3)
/A4: DD1.24 (A14), U1.34 (A4), U5.8 (B4)
/A5: DD1.32 (A15), U1.35 (A5), U5.9 (B5)
/A6: DD1.5 (A4), U1.36 (A6), U5.12 (B7)
/A7: DD1.4 (A3), U1.37 (A7), U5.14 (B1)
/A8: DD1.3 (A2), U1.38 (A8), U5.17 (B3)
/A9: DD1.2 (A1), U1.39 (A9), U5.20 (B5)
/A10: DD1.1 (A0), U1.40 (A10), U5.23 (B7)
/A11: DD1.35 (A18), U1.1 (A11), U5.22 (B6)
/A12: DD1.34 (A17), U1.2 (A12), U5.19 (B4)
/A13: DD1.33 (A16), U1.3 (A13), U5.16 (B2)
/A14: U1.4 (A14), U5.13 (B0)
/A15: U1.5 (A15), U5.11 (B6)
/BUSACK: U1.23 (~BUSACK~), U3.8 (B4)
/BUSRQ: U1.25 (~BUSRQ~), U3.16 (B2)
/CLK: U1.6 (~CLK~), U3.20 (B5)
/D0: DD1.12 (Q3), U1.14 (D0), U4.14 (B1)
/D1: DD1.25 (Q4), U1.15 (D1), U4.13 (B0)
/D2: DD1.11 (Q2), U1.12 (D2), U4.17 (B3)
/D3: DD1.30 (Q7), U1.8 (D3), U4.22 (B6)
/D4: DD1.7 (Q0), U1.7 (D4), U4.23 (B7)
/D5: DD1.8 (Q1), U1.9 (D5), U4.20 (B5)
/D6: DD1.29 (Q6), U1.10 (D6), U4.19 (B4)
/D7: DD1.26 (Q5), U1.13 (D7), U4.16 (B2)
/EXT0: J3.45, J4.5
/EXT1: J3.47, J4.6
/EXT2: J3.49, J4.7
/EXT3: J3.51, J4.8
/EXT4: J3.53, J4.9
/EXT5: J3.55, J4.10
/EXT6: J3.57, J4.11
/EXT7: J3.59, J4.12
/EXT8: J2.51, J4.18
/EXT9: J2.53, J4.16
/EXT10: J2.46, J4.20
/EXT11: J2.52, J4.19
/EXT12: J2.54, J4.17
/EXT13: J2.56, J4.15
/EXT14: J2.58, J4.14
/EXT15: J2.60, J4.13
/HALT: U1.18 (~HALT~), U3.9 (B5)
/INT: U1.16 (~INT~), U3.17 (B3)
/IORQ: U1.20 (~IORQ~), U3.3 (B1)
/M1: U1.27 (~M1~), U3.11 (B6)
/MA14: DD1.18 (A9), U4.2 (B0)
/MA15: DD1.20 (A10), U4.3 (B1)
/MA16: DD1.17 (A8), U4.5 (B2)
/MA17: DD1.21 (A11), U4.6 (B3)
/MA18: DD1.16 (A7), U4.8 (B4)
/MCE: DD1.6 (CE), U4.9 (B5)
/MOE: DD1.31 (OE), U4.11 (B6)
/MREQ: U1.19 (~MREQ~), U3.6 (B3)
/MWE: DD1.13 (WE), U4.12 (B7)
/NMI: U1.17 (~NMI~), U3.14 (B1)
/RD: U1.21 (~RD~), U3.2 (B0)
/RESET: U1.26 (~RESET~), U3.19 (B4)
/RFSH: U1.28 (~RFSH~), U3.12 (B7)
/WAIT: U1.24 (~WAIT~), U3.13 (B0)
/WR: U1.22 (~WR~), U3.5 (B2)
/ZA0: J3.31, U5.47 (A0)
/ZA1: J3.32, U5.46 (A1)
/ZA2: J3.29, U5.44 (A2)
/ZA3: J3.30, U5.43 (A3)
/ZA4: J3.27, U5.41 (A4)
/ZA5: J3.28, U5.40 (A5)
/ZA6: J3.26, U5.37 (A7)
/ZA7: J3.24, U5.35 (A1)
/ZA8: J3.22, U5.32 (A3)
/ZA9: J3.20, U5.29 (A5)
/ZA10: J3.18, U5.26 (A7)
/ZA11: J3.17, U5.27 (A6)
/ZA12: J3.19, U5.30 (A4)
/ZA13: J3.21, U5.33 (A2)
/ZA14: J3.23, U5.36 (A0)
/ZA15: J3.25, U5.38 (A6)
/ZBUSA: J2.32, U3.41 (A4)
/ZBUSRQ: J2.38, U3.33 (A2)
/ZCFG0: J3.46, R9.1, SW1.9
/ZCFG1: J3.48, R8.1, SW1.10
/ZCFG2: J3.50, R7.1, SW1.11
/ZCFG3: J3.52, R6.1, SW1.12
/ZCFG4: J3.54, R5.1, SW1.13
/ZCFG5: J3.56, R4.1, SW1.14
/ZCFG6: J3.58, R3.1, SW1.15
/ZCFG7: J3.60, R2.1, SW1.16
/ZCLK: J2.39, U3.29 (A5)
/ZD0: J3.40, U4.35 (A1)
/ZD1: J3.39, U4.36 (A0)
/ZD2: J3.38, U4.32 (A3)
/ZD3: J3.33, U4.27 (A6)
/ZD4: J3.34, U4.26 (A7)
/ZD5: J3.36, U4.29 (A5)
/ZD6: J3.35, U4.30 (A4)
/ZD7: J3.37, U4.33 (A2)
/ZDIR: J3.16, U4.24 (A->B)
/ZEX0: J2.55, R10.1, SW2.6
/ZEX1: J2.57, R11.1, SW2.5
/ZEX2: J2.59, R12.1, SW2.4
/ZHALT: J2.31, U3.40 (A5)
/ZINT: J2.37, U3.32 (A3)
/ZIORQ: J2.27, U3.46 (A1)
/ZM1: J2.34, U3.38 (A6)
/ZMA14: J2.42, U4.47 (A0)
/ZMA15: J2.41, U4.46 (A1)
/ZMA16: J2.44, U4.44 (A2)
/ZMA17: J2.43, U4.43 (A3)
/ZMA18: J3.43, U4.41 (A4)
/ZMCE: J3.44, U4.40 (A5)
/ZMOE: J3.41, U4.38 (A6)
/ZMREQ: J2.29, U3.43 (A3)
/ZMWE: J3.42, U4.37 (A7)
/ZNMI: J2.35, U3.35 (A1)
/ZRD: J2.28, U3.47 (A0)
/ZRESET: J2.40, U3.30 (A4)
/ZRFSH: J2.33, U3.37 (A7)
/ZWAIT: J2.36, U3.36 (A0)
/ZWR: J2.30, U3.44 (A2)
GND: C1.2, C2.2, C3.2, C4.2, C5.2, C6.2, C7.2, C8.2, C9.2, C10.2, C11.2, C12.2, C13.2, C14.2, C15.2, DD1.10 (VDD), DD1.28 (VDD), J1.2, J1.3, J2.1, J2.2, J2.5, J2.6, J2.61, J2.62, J3.1, J3.2, J3.5, J3.6, J3.61, J3.62, J4.3, J4.4, SW1.1, SW1.2, SW1.3, SW1.4, SW1.5, SW1.6, SW1.7, SW1.8, SW2.1, SW2.2, SW2.3, SW3.1, U1.29 (GND), U3.1 (A->B), U3.4 (GND), U3.10 (GND), U3.15 (GND), U3.21 (GND), U3.25 (CE), U3.28, U3.34 (GND), U3.39, U3.45 (GND), U3.48 (CE), U4.4 (GND), U4.10 (GND), U4.15 (GND), U4.21 (GND), U4.25 (CE), U4.28, U4.34 (GND), U4.39, U4.45 (GND), U4.48 (CE), U5.1 (A->B), U5.4 (GND), U5.10 (GND), U5.15 (GND), U5.21 (GND), U5.24 (A->B), U5.25 (CE), U5.28, U5.34 (GND), U5.39, U5.45 (GND), U5.48 (CE)
PUP: R13.1, U3.24 (A->B), U4.1 (A->B)
ZBRES: J2.45, R1.1, SW3.2

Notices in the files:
fpga/.test/orion.qsf:
Copyright (C) 2017  Intel Corporation. All rights reserved.
fpga/fpga_video/fpga_video.qsf:
Copyright (C) 2018  Intel Corporation. All rights reserved.
